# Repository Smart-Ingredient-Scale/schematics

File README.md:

# **ECE 477: Smart Kitchen Scale Schematics**

**Last Updated**: Mar 9, 2022

<h2 style="color: salmon" > <b> Repository Structure </b> </h2>

```
├── datasheets      # Directory for datasheets
├── docs            # file for library config
├── img             # Images folder for documentation
├── pcb             # Directory of schematics and board design files
└── README.md       

```

<h2 style="color: salmon" > <b> Schematic Design Responsibilities </b> </h2>

- [x] Design `Load Cell` subcircuit
- [x] Design `SPI Touchscreen` headers + &mu;C connections
- [x] Design `Battery Recharging` subcircuit
- [x] Design `Seven Segment Display` wire SPI pins + VDD/GND
- [x] Design `MCU Debugger` subcircuit
- [x] Integrate all submodules (MCU, battery, plugs, buttons, etc.)
- [x] Be a potato

<h2 style="color: salmon" > <b> Board Design Responsibilities </b> </h2>

- [x] Design PCB Revision 1.0.
- [ ] Verify PCB Revision 1.0 with course staff
- [ ] Order PCB via `JLCPCB` service
- [ ] Order a mask for component soldering via `JLCPCB` service

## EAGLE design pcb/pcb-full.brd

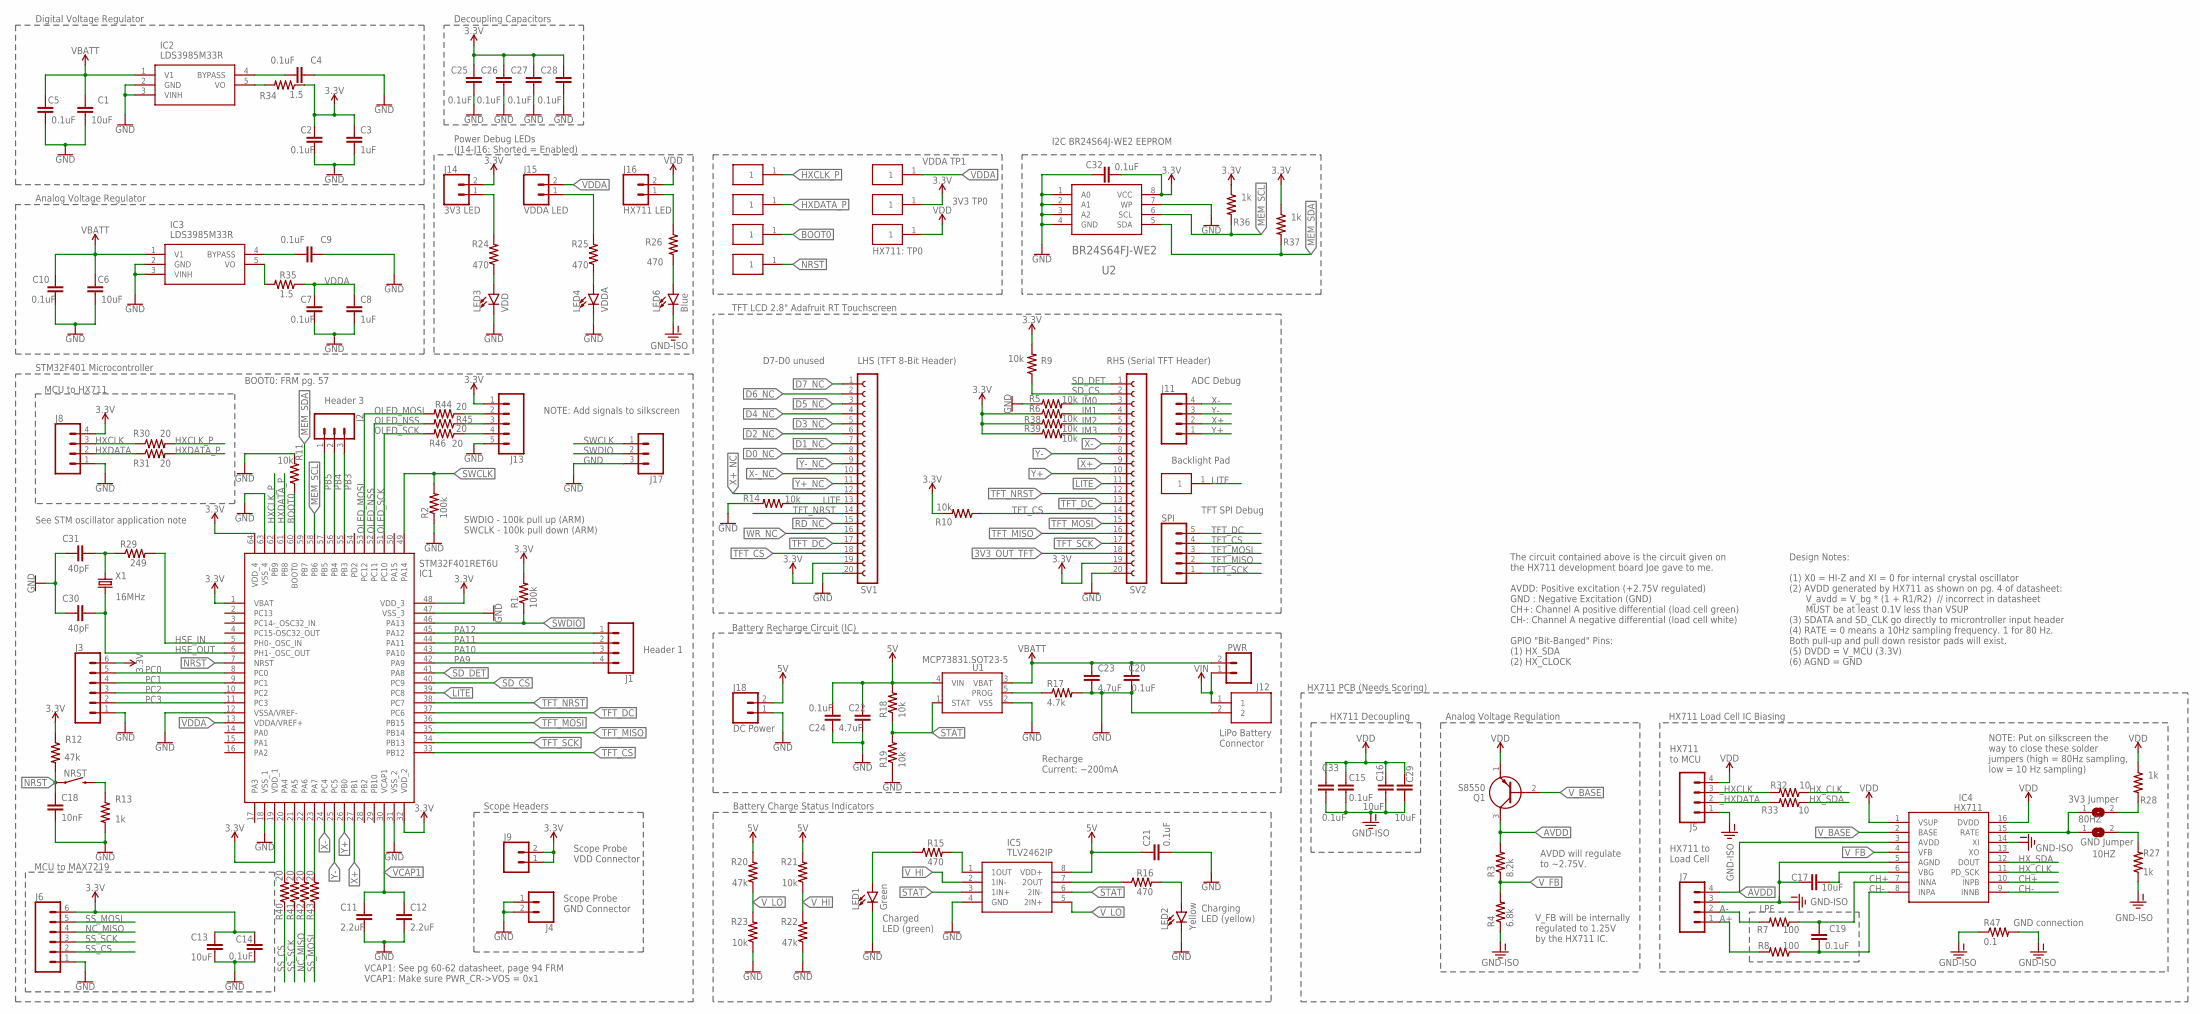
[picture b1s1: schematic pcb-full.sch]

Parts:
10HZ: GND Jumper; SJ
80HZ: 3V3 Jumper; SJ
C1, C6, C13, C16, C17, C29: 10uF; C0603
C2, C4, C5, C7, C9, C10, C14, C15, C19, C20, C21, C24, C25, C26, C27, C28, C32, C33: 0.1uF; C0603
C3, C8: 1uF; C0603
C11, C12: 2.2uF; C0603
C18: 10nF; C0603
C22, C23: 4.7uF; C5B4.5
C30, C31: 40pF; C0603
IC1: STM32F401RET6U; QFP50P1200X1200X160-64N
IC2, IC3: LDS3985M33R; SOT95P280X145-5N
IC4: HX711; SOIC127P600X160-16N
IC5: TLV2462IP; DIP794W53P254L959H508Q8N
J1, J5, J7, J8, J11: CONN_04; 1X04
J2, J17: CONN_03; 1X03
J3, J6: CONN_06SILK_FEMALE_PTH; 1X06
J4, J9: CONN_02; 1X02
J12: B2B-PH-K-S_LF__SN_; SHDR2W50P0X200_1X2_590X450X600
J13: CONN_05; 1X05
J14: 3V3 LED; 1X02
J15: VDDA LED; 1X02
J16: HX711 LED; 1X02
J18: DC Power; 1X02
LED1: Green; LED-0603
LED2: Yellow; LED-0603
LED3: VDD; LED-0603
LED4: VDDA; LED-0603
LED6: Blue; LED-0603
NRST: MOMENTARY-SWITCH-SPST-SMD-5.2-REDUNDANT; TACTILE_SWITCH_SMD_5.2MM
PWR: CONN_02; 1X02
Q1: S8550; MJE13001TP
R1, R2: 100k; R0603
R3: 8.2k; R0603
R4: 6.8k; R0603
R5, R6, R9, R10, R11, R14, R18, R19, R21, R23, R38, R39: 10k; R0603
R7, R8: 100; R0603
R12, R20, R22: 47k; R0603
R13, R27, R28, R36, R37: 1k; R0603
R15, R16, R24, R25, R26: 470; R0603
R17: 4.7k; R0603
R29: 249; R0603
R30, R31, R40, R41, R42, R43, R44, R45, R46: 20; R0603
R32, R33: 10; R0603
R34, R35: 1.5; R0603
R47: 0.1; R0603
SPI: CONN_05; 1X05
SV1: LHS (TFT 8-Bit Header); FE20
SV2: RHS (Serial TFT Header); FE20
U1: MCP73831.SOT23-5; SOT23-5
U2: BR24S64FJ-WE2; SOIC8
U$1, U$6: TP1; PAD
U$2: TP3; PAD
U$3: TP4; PAD
U$4: TP5; PAD
U$5: TP6; PAD
U$7: TP0; PAD
U$8: TP2; PAD
X1: 16MHz; HC49/S

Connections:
3.3V: C2.1, C3.1, C13.1, C14.1, C25.1, C26.1, C27.1, C28.1, C32.2, IC1.1 (VBAT), IC1.19 (VDD_1), IC1.32 (VDD_2), IC1.48 (VDD_3), IC1.64 (VDD_4), J3.6, J6.6, J8.4, J9.1, J9.2, J13.1, J14.2, R1.2, R6.1, R9.2, R10.2, R12.1, R34.1, R36.1, R37.1, R38.1, R39.1, SV1.19, SV2.19, U2.8 (VCC), U$7.1
3V3_LED: J14.1, R24.2
3V3_OUT_TFT: SV2.18
5V: C21.1, C22.1, C24.2, IC5.8 (VDD+), J18.2, R18.2, R20.2, R21.2, U1.4 (VIN)
A+: J7.1, R8.2
A-: J7.2, R7.2
ANA_LED: J15.1, R25.2
AVDD: IC4.3 (AVDD), J7.4, Q1.3 (C), R3.2
BOOT0: IC1.60 (BOOT0), R11.1, U$4.1
CH+: C19.1, IC4.7 (INNA), IC4.10 (INPB), R7.1
CH-: C19.2, IC4.8 (INPA), IC4.9 (INNB), R8.1
D0_NC: SV1.8
D1_NC: SV1.7
D2_NC: SV1.6
D3_NC: SV1.5
D4_NC: SV1.4
D5_NC: SV1.3
D6_NC: SV1.2
D7_NC: SV1.1
GND: C1.2, C2.2, C3.2, C4.1, C5.2, C6.2, C7.2, C8.2, C9.1, C10.2, C11.2, C12.2, C13.2, C14.2, C18.2, C20.2, C21.2, C22.2, C23.2, C24.1, C25.2, C26.2, C27.2, C28.2, C30.1, C31.1, C32.1, IC1.12 (VSSA/VREF-), IC1.18 (VSS_1), IC1.31 (VSS_2), IC1.47 (VSS_3), IC1.63 (VSS_4), IC2.2 (GND), IC2.3 (VINH), IC3.2 (GND), IC3.3 (VINH), IC5.4 (GND), J3.1, J4.1, J4.2, J6.1, J8.1, J12.2, J13.5, J17.3, J18.1, LED1.C, LED2.C, LED3.C, LED4.C, R2.1, R5.1, R11.2, R13.2, R14.2, R17.2, R19.1, R22.1, R23.1, SV1.20, SV2.20, U1.2 (VSS), U2.1 (A0), U2.2 (A1), U2.3 (A2), U2.4 (GND), U2.7 (WP)
GND-ISO: C15.2, C16.2, C17.1, C29.2, C33.2, IC4.5 (AGND), IC4.14 (XI), J5.1, J7.3, LED6.C, R4.1, R27.1, R47.1, R47.2
HSE_IN: IC1.5 (PH0-_OSC_IN), R29.2
HSE_OUT: C30.2, IC1.6 (PH1-_OSC_OUT), X1.1
HXCLK: J8.3, R30.1
HXCLK_P: IC1.62 (PB9), R30.2, U$2.1
HXDATA: J8.2, R31.1
HXDATA_P: IC1.61 (PB8), R31.2, U$3.1
HX_CLK: IC4.11 (PD_SCK), R32.1
HX_LED: J16.1, R26.1
HX_SDA: IC4.12 (DOUT), R33.1
IM0: R5.2, SV2.3
IM1: R6.2, SV2.4
IM2: R38.2, SV2.5
IM3: R39.2, SV2.6
LITE: IC1.39 (PC8), R14.1, SV1.13, SV2.11, U$1.1
MEM_SCL: IC1.58 (PB6), R36.2, U2.6 (SCL)
MEM_SDA: IC1.59 (PB7), R37.2, U2.5 (SDA)
unnamed: C9.2, IC3.4 (BYPASS)
unnamed: LED1.A, R15.1
unnamed: C4.2, IC2.4 (BYPASS)
unnamed: IC5.7 (2OUT), R16.1
unnamed: LED2.A, R16.2
unnamed: IC5.1 (1OUT), R15.2
unnamed: R17.1, U1.5 (PROG)
unnamed: J13.2, R44.1
unnamed: LED4.A, R25.1
unnamed: 10HZ.2, R27.2
unnamed: C17.2, IC4.6 (VBG)
unnamed: 10HZ.1, 80HZ.1, IC4.15 (RATE)
unnamed: LED3.A, R24.1
unnamed: LED6.A, R26.2
unnamed: IC3.5 (VO), R35.2
unnamed: 80HZ.2, R28.2
unnamed: NRST.3 (2), NRST.4 (2), R13.1
unnamed: C31.2, R29.1, X1.2
unnamed: IC2.5 (VO), R34.2
unnamed: J13.3, R45.1
unnamed: J13.4, R46.1
NC_MISO: J6.4, R42.1
NRST: C18.1, IC1.7 (NRST), NRST.1, NRST.2 (1), R12.2, U$5.1
OLED_MOSI: IC1.53 (PC12), R44.2
OLED_NSS: IC1.52 (PC11), R45.2
OLED_SCK: IC1.51 (PC10), R46.2
PA9: IC1.42 (PA9), J1.4
PA10: IC1.43 (PA10), J1.3
PA11: IC1.44 (PA11), J1.2
PA12: IC1.45 (PA12), J1.1
PB3: IC1.55 (PB3), J2.3
PB4: IC1.56 (PB4), J2.2
PB5: IC1.57 (PB5), J2.1
PC0: IC1.8 (PC0), J3.5
PC1: IC1.9 (PC1), J3.4
PC2: IC1.10 (PC2), J3.3
PC3: IC1.11 (PC3), J3.2
RD_NC: SV1.15
SD_CS: IC1.40 (PC9), R9.1, SV2.2
SD_DET: IC1.41 (PA8), SV2.1
SS_CS: J6.2, R40.1
SS_MOSI: J6.5, R43.1
SS_SCK: J6.3, R41.1
STAT: IC5.3 (1IN+), IC5.6 (2IN-), R18.1, R19.2, U1.1 (STAT)
SWCLK: IC1.49 (PA14), J17.1, R2.2
SWDIO: IC1.46 (PA13), J17.2, R1.1
TFT_CS: IC1.33 (PB12), R10.1, SPI.4, SV1.18, SV2.14
TFT_DC: IC1.37 (PC6), SPI.5, SV1.17, SV2.13
TFT_MISO: IC1.35 (PB14), SPI.2, SV2.16
TFT_MOSI: IC1.36 (PB15), SPI.3, SV2.15
TFT_NRST: IC1.38 (PC7), SV1.14, SV2.12
TFT_SCK: IC1.34 (PB13), SPI.1, SV2.17
VCAP1: C11.1, C12.1, IC1.30 (VCAP1)
VDD: C15.1, C16.1, C29.1, C33.1, IC4.1 (VSUP), IC4.16 (DVDD), J5.4, J16.2, Q1.1 (E), R28.1, U$8.1
VDDA: C7.1, C8.1, IC1.13 (VDDA/VREF+), J15.2, R35.1, U$6.1
VIN: J12.1, PWR.1
V_BASE: IC4.2 (BASE), Q1.2 (B)
V_BATT: C1.1, C5.1, C6.1, C10.1, C20.1, C23.1, IC2.1 (V1), IC3.1 (V1), PWR.2, U1.3 (VBAT)
V_FB: IC4.4 (VFB), R3.1, R4.2
V_HI: IC5.2 (1IN-), R21.1, R22.2
V_LO: IC5.5 (2IN+), R20.1, R23.2
WR_NC: SV1.16
X+: IC1.27 (PB1), J11.2, SV2.9
X+_NC: SV1.12
X-: IC1.24 (PC4), J11.4, SV2.7
X-_NC: SV1.10
Y+: IC1.26 (PB0), J11.1, SV2.10
Y+_NC: SV1.11
Y-: IC1.25 (PC5), J11.3, SV2.8
Y-_NC: SV1.9
_HXCLK: J5.3, R32.2
_HXDATA: J5.2, R33.2
_NC_MISO: IC1.22 (PA6), R42.2
_SS_CS: IC1.20 (PA4), R40.2
_SS_MOSI: IC1.23 (PA7), R43.2
_SS_SCK: IC1.21 (PA5), R41.2

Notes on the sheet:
Analog Voltage Regulator
Digital Voltage Regulator
SWDIO - 100k pull up (ARM) SWCLK - 100k pull down (ARM)
Header 1
Header 3
HX711 to MCU
The circuit contained above is the circuit given on the HX711 development board Joe gave to me. AVDD: Positive excitation (+2.75V regulated) GND : Negative Excitation (GND) CH+: Channel A positive differential (load cell green) CH-: Channel A negative differential (load cell white) GPIO "Bit-Banged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
HX711 Decoupling
Design Notes: (1) X0 = HI-Z and XI = 0 for internal crystal oscillator (2) AVDD generated by HX711 as shown on pg. 4 of datasheet: V_avdd = V_bg * (1 + R1/R2) // incorrect in datasheet MUST be at least 0.1V less than VSUP (3) SDATA and SD_CLK go directly to microntroller input header (4) RATE = 0 m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
Analog Voltage Regulation
V_FB will be internally regulated to 1.25V by the HX711 IC.
HX711 Load Cell IC Biasing
NOTE: Put on silkscreen the way to close these solder jumpers (high = 80Hz sampling, low = 10 Hz sampling)
AVDD will regulate to ~2.75V.
HX711 to Load Cell
STM32F401 Microcontroller
Scope Probe GND Connector
MCU to HX711
HX711 PCB (Needs Scoring)
D7-D0 unused
TFT LCD 2.8" Adafruit RT Touchscreen
MCU to MAX7219
Scope Probe VDD Connector
ADC Debug
Backlight Pad
TFT SPI Debug
Scope Headers
NOTE: Add signals to silkscreen
LPF
VCAP1: See pg 60-62 datasheet, page 94 FRM VCAP1: Make sure PWR_CR->VOS = 0x1
Charging LED (yellow)
Charged LED (green)
Recharge Current: ~200mA
Battery Charge Status Indicators
Battery Recharge Circuit (IC)
LiPo Battery Connector
Power Debug LEDs (J14-J16: Shorted = Enabled)
Decoupling Capacitors
BOOT0: FRM pg. 57
See STM oscillator application note

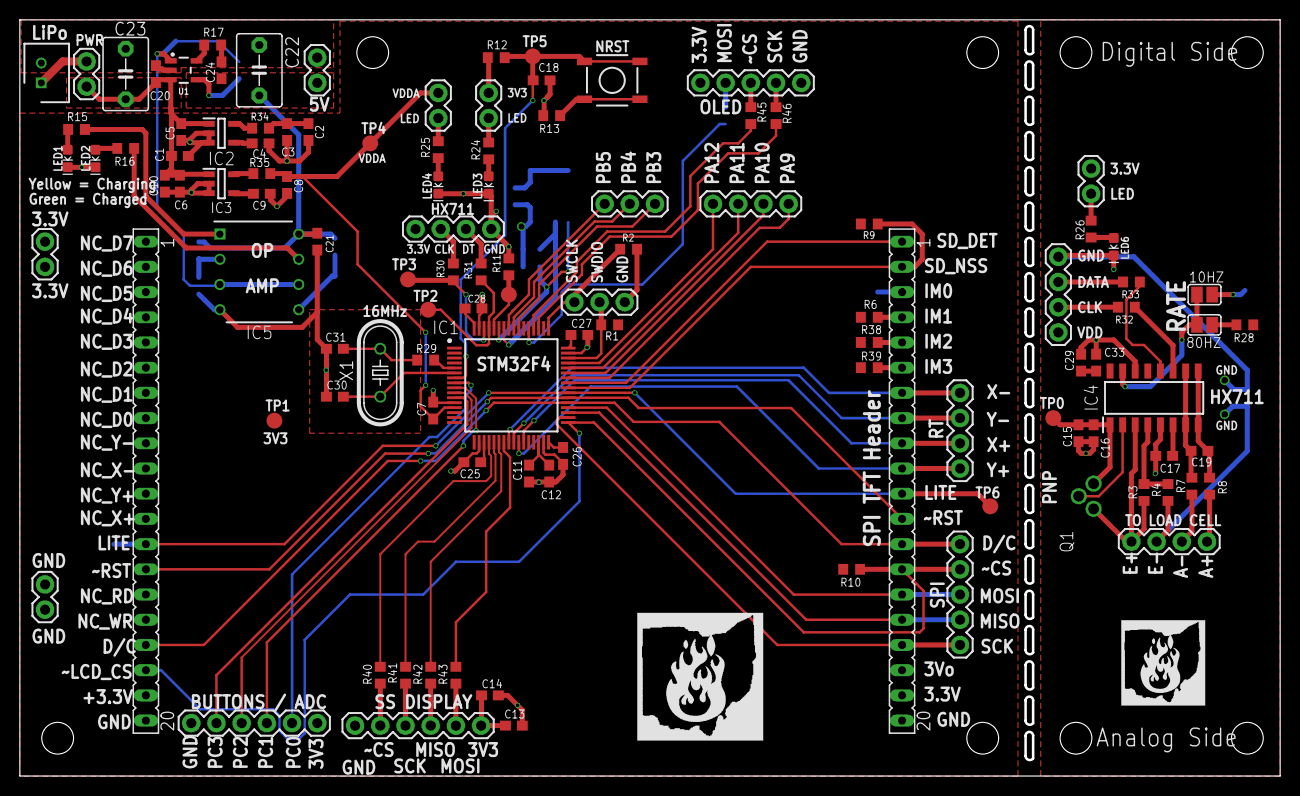
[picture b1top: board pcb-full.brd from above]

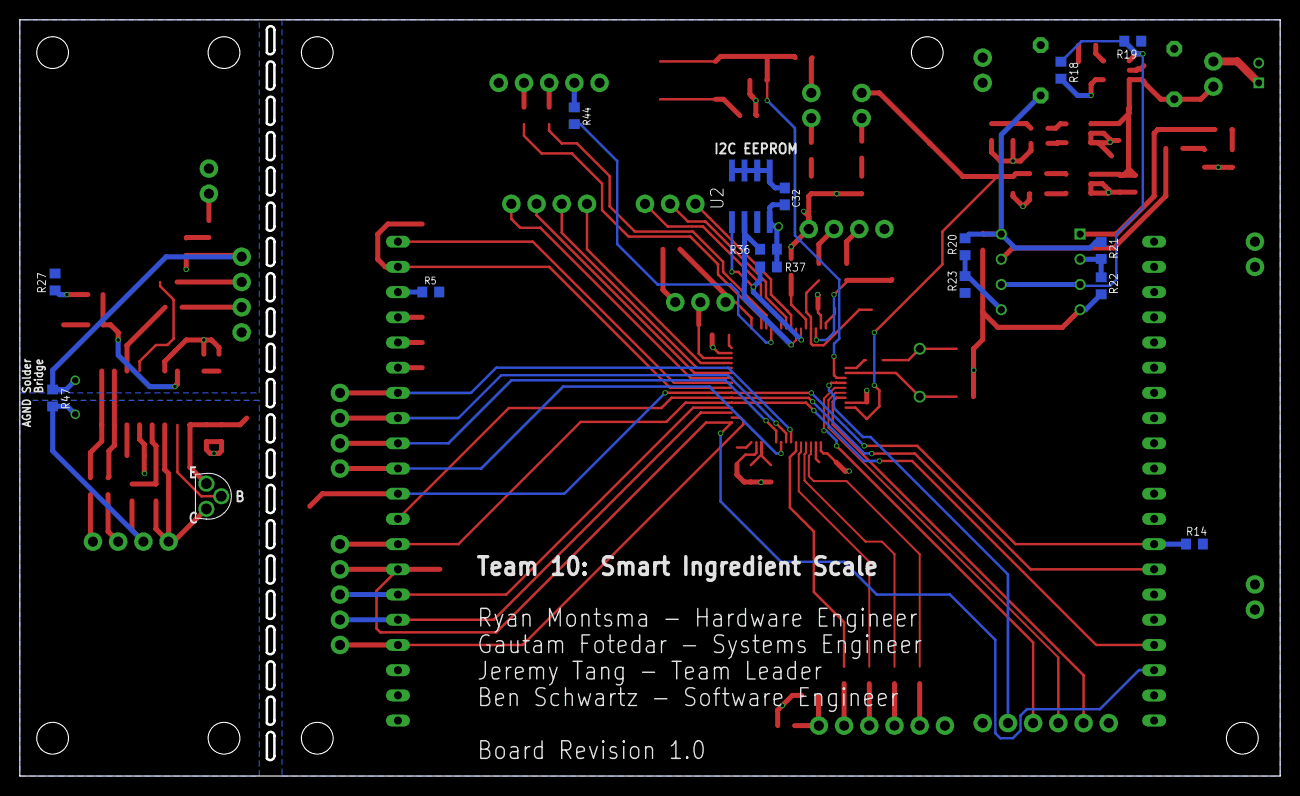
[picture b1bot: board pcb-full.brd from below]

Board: 2 copper layers, 127.0 x 76.2 mm, 128 parts (16 on the bottom side), 98 nets.

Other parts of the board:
U$9: BURNING-OHIO
U$10: BURNING-OHIO2

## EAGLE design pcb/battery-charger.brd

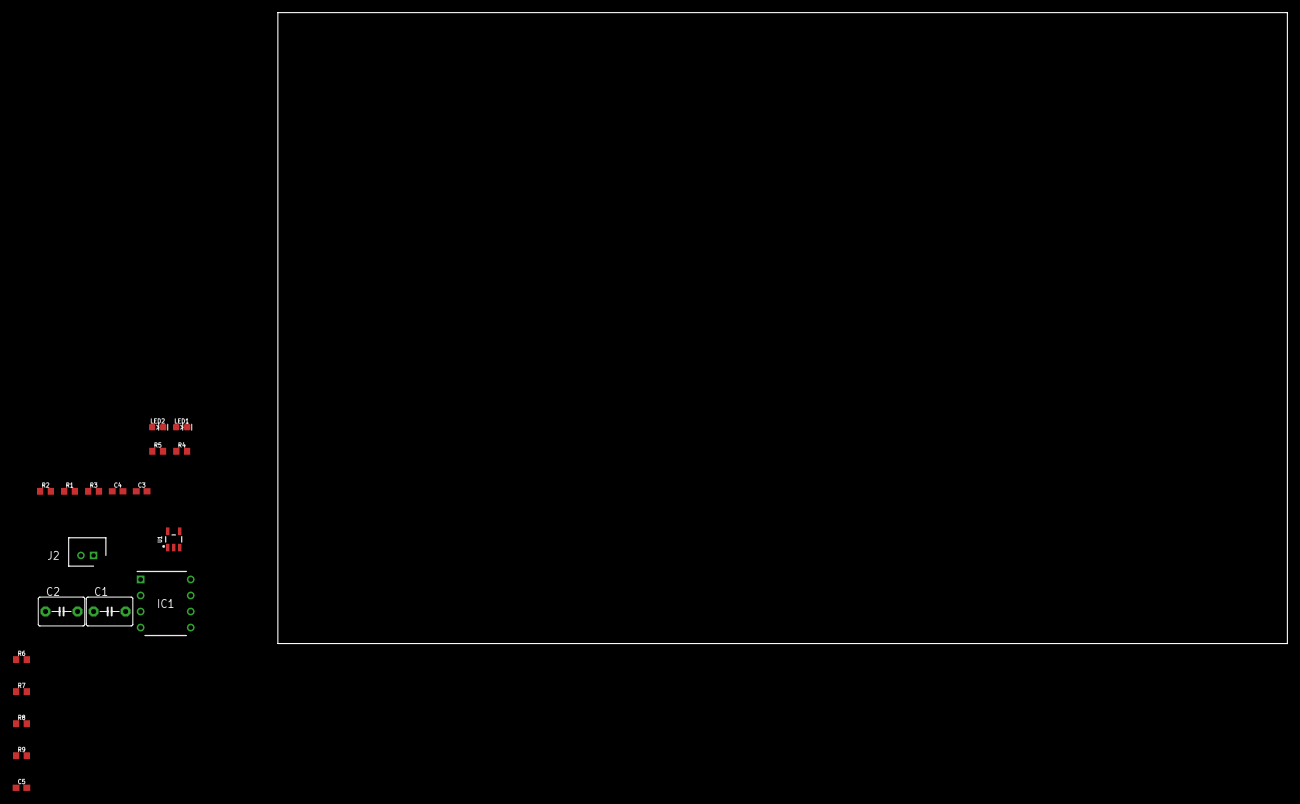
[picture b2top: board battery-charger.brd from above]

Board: 2 copper layers, 160.0 x 100.0 mm, 19 parts (0 on the bottom side), 11 nets, no tracks yet.

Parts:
C1, C2: 4.7uF; C5B4.5
C3, C4, C5: 0.1uF; C0603
IC1: TLV2462IP; DIP794W53P254L959H508Q8N
J2: B2B-PH-K-S_LF__SN_; SHDR2W50P0X200_1X2_590X450X600
LED1, LED2: LED-0603
R1: 330; R0603
R2: 470; R0603
R3: 4.7k; R0603
R4, R5, R7, R9: 10k; R0603
R6, R8: 47k; R0603
U1: MCP73831.SOT23-5; SOT23-5

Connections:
5V: C1.1, C4.1, C5.2, IC1.8, R4.2, R6.2, R7.2, U1.4
GND: C1.2, C2.2, C3.2, C4.2, C5.1, IC1.4, J2.2, LED1.C, LED2.C, R3.2, R5.1, R8.1, R9.1, U1.2
unnamed: IC1.1, R1.2
unnamed: LED1.A, R1.1
unnamed: IC1.7, R2.1
unnamed: LED2.A, R2.2
unnamed: R3.1, U1.5
STAT: IC1.3, IC1.6, R4.1, R5.2, U1.1
V_BATT: C2.1, C3.1, J2.1, U1.3
V_HI: IC1.2, R7.1, R8.2
V_LO: IC1.5, R6.1, R9.2

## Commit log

2022-01-19 Initialized the schematics repository w/ basic directory structure
2022-02-02 Updated the EAGLE schematic for the battery recharging circuit: verified
2022-02-02 Updated the battery recharging subcircuit documentation
2022-02-16 Updated the footprints barring the TLV2462 op amp and improper header
2022-02-16 Updated all relevent datasheets and images (pinouts). Need to summarize in README.md.
2022-02-23 Updated the PCB Schematic: 80% complete. Added PCB reference.
2022-02-23 Cleaned up the junk files
2022-02-25 Updated the schematic: Power supply and EEPROM: TBD
2022-02-26 Updated the PCB board and schematic. In process of generally laying down components. Will be working on the design for next 1.5 hours.
2022-02-26 Updated the micro-board.brd file with power supply + basic polygons
2022-02-26 Added first, somewhat flawed EEPROM footprint
2022-02-26 Updated power supply, decoupling, analog and digital GND
2022-02-27 Updated I2C-EEPROM board footprint for pin renaming
2022-02-27 Final update to the I2C EEPROM lbr
2022-02-28 Final update to the I2C EEPROM lbr - Added necessary connection between schematic and pins
2022-02-28 Added I2C EEPROM Footprint to both schematic and board and dimensioned appropriately
2022-02-28 Finished simplistic EEPROM routing on back of main board
2022-02-28 Updated EEPROM Resistor Positions
2022-02-28 Incremental commit of changes
2022-02-28 Adding b&w footprint to scale
2022-02-28 Add Documentation for schematic and footprints
2022-03-01 Continued Routing (more in longer description)
    Added these subsystems routed:
    nrst for reset switch.
    HXDATA and HXCLK for the Micro's header.
    Boot0 pad
    Scope probe headers for GND and 3.3V
2022-03-01 Updated TFT right-side header, debug headers, and routing
2022-03-01 Incremental commit of changes made
2022-03-01 Further PCB development
2022-03-02 Updated the initial revision of the PCB + PDFs of layout
2022-03-02 Removed the garbage files
2022-03-09 Updated the PCB with more silkscreen and ESD protection resistors
2022-03-09 Updated directory structure, cleaned up PCB, and updated README
2022-03-09 Updated the 8 mil trace clearance and DRC
2022-03-10 Final version of the PCB? Updated headers + silkscreen + AGND
2022-03-11 Finished updating the PCB + Gerber files zip file
2022-03-11 Updated the Gerber files (unzipped the archive)

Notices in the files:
parts and their libraries:
SparkFun-Switches: Licensing: Creative Commons ShareAlike 4.0 International - https://creativecommons.org/licenses/by-sa/4.0
